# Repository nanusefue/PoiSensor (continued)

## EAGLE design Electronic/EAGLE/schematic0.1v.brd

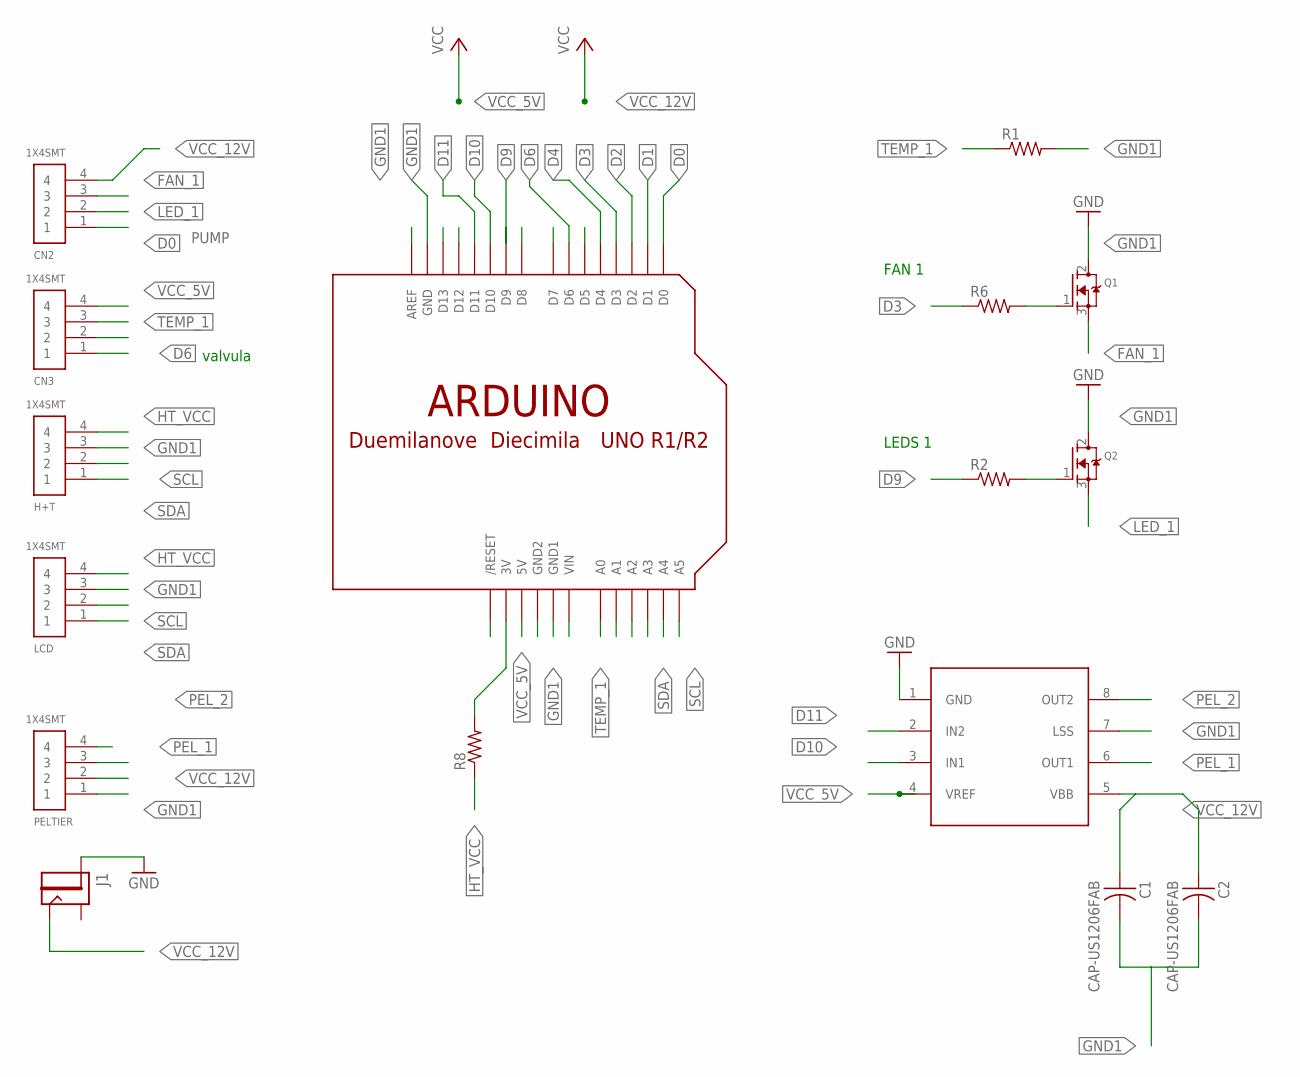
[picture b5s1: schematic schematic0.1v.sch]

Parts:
C1, C2: CAP-US1206FAB; C1206FAB
CN2, CN3: 1X4SMT; 1X4-SMT
H+T: 1X4SMT; 1X4-SMT
J1: JACK2.1MM; JACK_2.1MM
LCD: 1X4SMT; 1X4-SMT
PELTIER: 1X4SMT; 1X4-SMT
Q1, Q2: MOSFET-NGDS_TO220V; TO220V
R1, R2, R6, R8: RES-US1206; R1206
U$1: ARDUINOUNO; ARDUINO
U$2: A4953-H-BRIDGE-MOTOR-DRIVER; SOIC8

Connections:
D0: CN2.1, U$1.D0
D1: U$1.D1
D2: U$1.D2
D3: R6.1, U$1.D3
D4: U$1.D4
D6: CN3.2, U$1.D6
D9: R2.1, U$1.D9
D10: U$1.D10, U$2.3 (IN1)
D11: U$1.D11, U$2.2 (IN2)
FAN_1: CN2.3, Q1.3 (S)
GND1: C1.2, C2.2, H+T.3, J1.PIN, LCD.3, PELTIER.1, Q1.2 (D), Q2.2 (D), R1.2, U$1.GND, U$1.GND2, U$2.1 (GND), U$2.7 (LSS)
HT_VCC: H+T.4, LCD.4, R8.1
LED_1: CN2.2, Q2.3 (S)
unnamed: Q1.1 (G), R6.2
unnamed: Q2.1 (G), R2.2
unnamed: R8.2, U$1.3V
PEL_1: PELTIER.3, U$2.6 (OUT1)
PEL_2: PELTIER.4, U$2.8 (OUT2)
SCL: H+T.2, LCD.2, U$1.A5
SDA: H+T.1, LCD.1, U$1.A4
TEMP_1: CN3.3, R1.1, U$1.A0
VCC_5V: CN3.4, U$1.5V, U$2.4 (VREF)
VCC_12V: C1.1, C2.1, CN2.4, J1.CONTACT, PELTIER.2, U$2.5 (VBB)

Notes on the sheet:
FAN 1
LEDS 1
PUMP
valvula

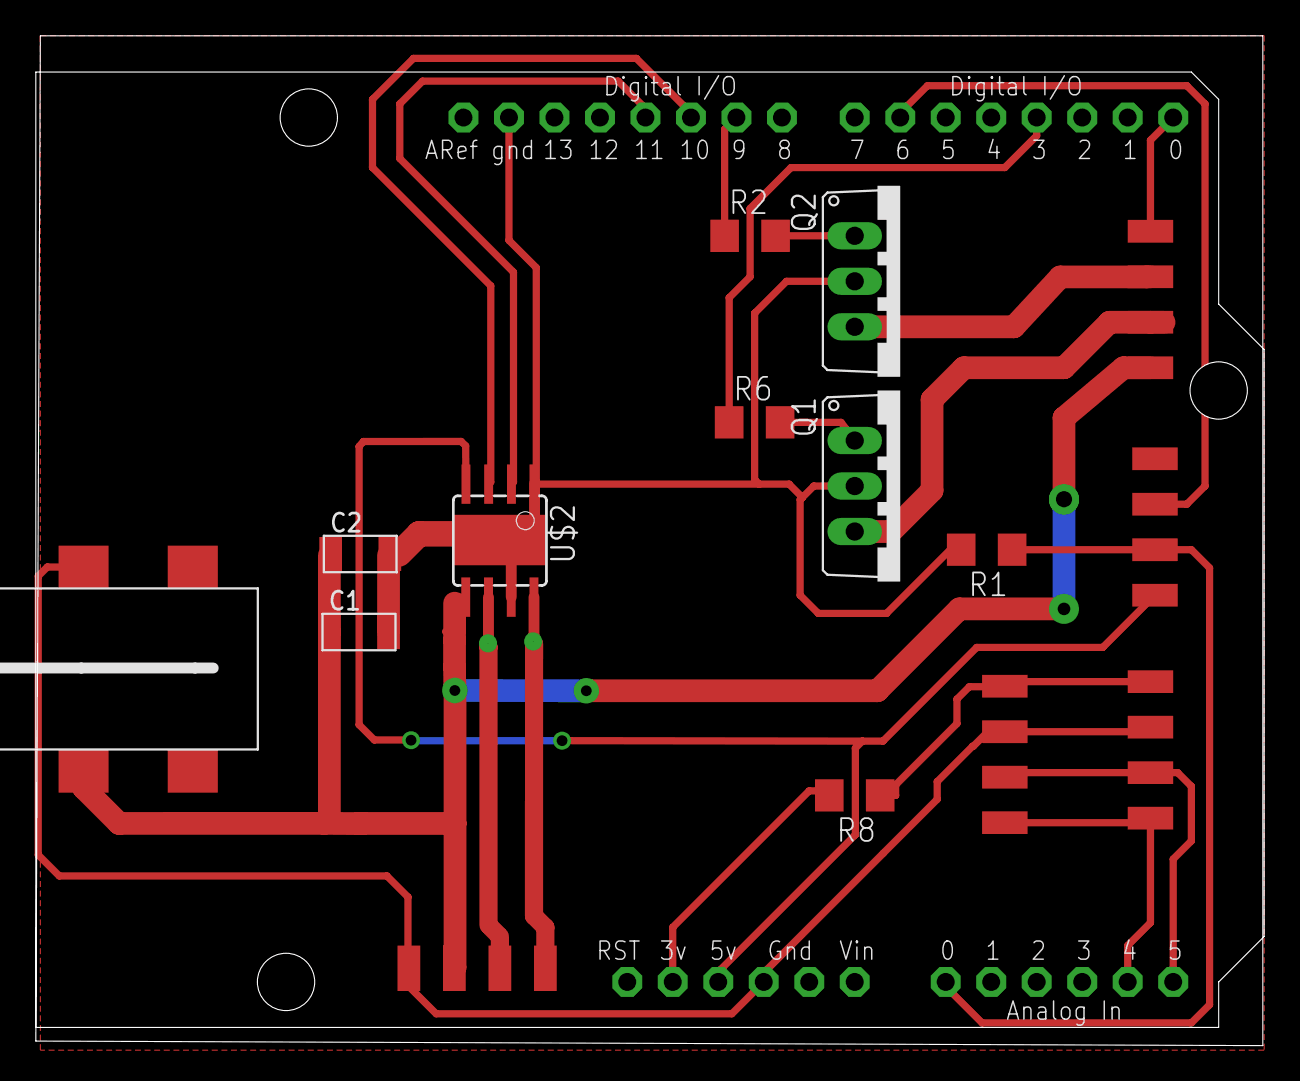
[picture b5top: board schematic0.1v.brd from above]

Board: 2 copper layers, 68.6 x 56.4 mm, 16 parts (0 on the bottom side), 20 nets.

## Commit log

2016-12-21 file estructure
2016-12-21 add sensor
2017-01-08 beta version h-bridgh
2017-01-10 nueva vetrsion
2017-01-11 new version
2017-01-12 fix box
2017-01-12 add new version change pn heade, fix plug vcc
2017-05-10 nueva version pelgiert
2017-05-10 version Pi
2017-05-11 nueva version Pi
2017-06-12 seedstudio finish
2017-06-12 seeed
2017-06-22 asda
2017-10-17 update board
2018-03-13 clean files
